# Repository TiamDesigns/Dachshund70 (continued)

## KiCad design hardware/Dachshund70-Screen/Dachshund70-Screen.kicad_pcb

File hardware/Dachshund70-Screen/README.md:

# Dachshund70 screen board

A small board that powers the 2.7" Sharp memory LCD and joins it to the mainboard with one flat cable. KiCad 10
project, 2 layers, 0.8 mm FR4, 21.0 × 34.0 mm with R1 corners.

- **Panel:** Sharp LS027B7DH01 (400 × 240, 2.7", 62.8 × 42.82 × 1.64 mm glass, 58.8 × 35.28 mm picture, about
  173 ppi). It stands on end beside the knob, so the picture is 240 × 400 in portrait. A memory LCD redraws a
  full frame in about 50 ms and holds its picture for a few microwatts, so the firmware treats it like an OLED,
  not like e-paper: no refresh limit, no flashing.
- **Every part is on the bottom side**, facing the mainboard. The top side is a plain ground pour, taped to the
  back of the panel.
- **Same coordinates as the mainboard.** The board is drawn where it sits in the case, straight over the
  mainboard (x 311.0 to 332.0, y 69.2 to 103.2 KiCad mm), so its STEP drops into the case model at the same x
  and y (`python hardware/export_step.py` writes `hardware/step/Dachshund70-Screen.step` with the mainboard's
  origin).

Rev 1.0 of this board (in git history, PR #83) drove the 2.13" GDEY0213B74 e-paper panel instead.

## Circuit

- **5 V supply.** The panel runs from 5 V (VDD and VDDA, 4.8 to 5.5 V). U1, a TI TPS61222 (fixed 5 V boost,
  SC-70-6), makes it from the mainboard's 3V3, with L1 (4.7 µH), C1 (10 µF in) and C2 (10 µF out), as in TI's
  5 V example. FB goes straight to VOUT, as the datasheet says for the fixed versions.
- **Enable.** U1's EN comes from J4 pin 8 (the e-paper overlays' BUSY, P0.24) as VLCD_EN, and R1 (100 kΩ) pulls
  it up to 3V3. The Sharp overlay leaves that pin alone, so the 5 V is always on. The firmware could drive it low
  to cut the panel's power in deep sleep, but then the panel loses its picture.
- **Logic.** The panel takes 3.3 V logic straight (VIH from 2.7 V; Sharp recommends about 3 V). No level shifter.
- **VCOM.** EXTMODE is tied high, so VCOM follows the EXTCOMIN pulse from the MCU (Zephyr's `sharp,ls0xx` driver
  toggles it at 1 Hz).
- **Sharp's capacitors.** C3 (1 µF, VDD), C4 (100 nF, VDDA) and C5 (100 nF, DISP), placed close to J1.
- **Power.** The panel draws about 50 µW holding a picture and about 175 µW updating once a second. With U1's
  5.5 µA quiescent current, the screen costs about 0.03 to 0.08 mA while typing and 20 to 40 µA asleep.

The firmware build is
`-DEXTRA_DTC_OVERLAY_FILE=displays/sharp-ls027b7dh01-portrait.overlay`.

## Cable

The mainboard's J4 is an 8-pin 0.5 mm FFC socket (Hirose FH12-8S-0.5SH(55)), on its top side under the plate's
screen notch. The screen board's J2 is the same socket on its bottom side, at the same x and y (centre
(327.9, 94.9)). Both mouths face −x. The cable leaves J4, loops up through the plate's notch and turns back into
J2: a C-shaped loop.

- Use a **0.5 mm pitch, 8-way FFC with contacts on the same side at both ends** (often called type A). Each
  conductor stays at the same y, so J4 pin n meets J2 pin 9 − n. The schematics already account for that.
- The length still has to be set from the case model: the gap between the two boards plus the loop. Buy a
  few lengths around it; FFCs are cheap.

J4 and the mainboard are unchanged from rev 1.0. Its pins keep their e-paper names in the mainboard schematic; the
Sharp panel uses them like this:

| J4 pin (mainboard) | Mainboard net | MCU pin | J2 pin (screen board) | Screen board net | Panel pin |
| --- | --- | --- | --- | --- | --- |
| 1 | +3V3 | | 8 | +3V3 (U1 input) | |
| 2 | GND | | 7 | GND | 9, 10 |
| 3 | DISP_DIN | P0.21 | 6 | SI | 2 |
| 4 | DISP_CLK | P0.19 | 5 | SCLK | 1 |
| 5 | DISP_CS | P0.20 | 4 | SCS (active high) | 3 |
| 6 | DISP_DC | P0.23 | 3 | EXTCOMIN | 4 |
| 7 | DISP_RST | P0.22 | 2 | DISP | 5 |
| 8 | DISP_BUSY | P0.24 | 1 | VLCD_EN (U1's EN) | |

Panel pins 6 and 7 (VDDA, VDD) and 8 (EXTMODE) are on +5V.

## Geometry

- **The panel's tail.** In landscape the LS027B7DH01's FPC leaves a long edge (the bottom one). Stood on end, that
  edge is on the left. The tail folds back under the glass (Sharp allows bends 0.8 to 6.0 mm from the glass edge,
  inner radius at least 0.45 mm) and runs right into J1.
- **J1** (panel socket, Hirose FH12-10S-0.5SH(55)) is centred at (316.6, 93.7) with its mouth facing −x, toward
  the board's left edge. Its pad row is at x 318.45, from pad 10 at y 91.45 to pad 1 at y 95.95.
- **J1's pins run the other way from the panel's: J1 pin n = panel pin 11 − n.** Looking down on the board,
  the fold puts panel pin 1 at the top (smaller y), where J1's pad 10 is. That assumes pin 1 is on the left of
  the tail when you look at the panel's face in landscape with the tail at the bottom: check it (see below).
- **J2** (cable socket) has its pad row at x 329.75, y 93.15 (pin 8, 3V3) to 96.65 (pin 1, VLCD_EN).
- The board stays left of the radio's antenna (x > 333) and well inside the glass (about x 308 to 351 and y 62
  to 125, if the case thread's 39 mm sidebar holds).

## Routing

The board is hand-routed in `gen_screen.py`.

- The five signals run right from J1, then step down a staircase into J2 under its body. SCLK and SI swap
  order between the two sockets, so SCLK hops over SI on the top layer: the only crossing.
- The boost sits above the sockets: U1 in the middle, L1 to its left, C1 and the 3V3 rail above.
- 3V3 runs from J2 up the right-hand side under J2's body, then along the top of the board.
- On the top layer, apart from the SCLK hop, two tracks cross the ground pour: +5V from the boost down to J1
  and its capacitors, and VLCD_EN from J2 up to U1.
- Track widths are 0.4 mm for SW, 0.3 mm for 3V3, +5V and ground stubs, 0.2 mm for signals. Vias are
  0.6/0.3 mm.

## Mainboard changes

None for the Sharp panel. J4 became an FFC socket in rev 1.0; `move_j4.py` records that one-off edit.

## Status

The board has been checked in KiCad only. Nothing is ordered, made or fitted.

- ERC: 0. DRC with schematic parity and every severity: 0 violations and 0 unconnected items.

## Open checks before ordering

- **Panel FPC: pin 1, contact face and pitch.** From Sharp's drawing, or a panel in hand: which end of the tail
  is pin 1, which face carries the contacts, and the pitch (0.5 mm is assumed). If pin 1 lands at the bottom of
  J1 instead, swap J1's pin map in `gen_screen.py` (`SOCKET`) and reroute. Then check the FH12-10S's contact side
  against the tail's contacts after the fold. Sharp's recommended sockets are SMK CFP-4610-0150F (bottom
  contact) and Molex 51441-1093.
- **Panel tail position and length.** Where along the long edge the tail leaves, and how long it is, so that
  it reaches J1 after the fold. J1 sits at y 93.7, about the middle of the glass's length.
- **FFC against the sockets.** As in rev 1.0: with same-side contacts and the C-shaped loop, J2 and J4 must
  have their contacts on the same side as the cable's contacts at each end.
- **LCSC numbers to confirm or fill:**
  - Filled in: 10 µF C19702, 1 µF C52923, 100 nF C1525, 100 kΩ C25741. Confirm these.
  - Still blank: J1 and J2 (FH12-10S and FH12-8S), U1 (TPS61222DCKR) and L1 (FNR3015S4R7MT).
- **Case.** The screen pocket, window and board pocket in the Fusion model are drawn for the 2.13" e-paper. They
  need the LS027B7DH01's 62.8 × 42.82 mm glass, the folded tail on the left, and this board under it. Then place
  the FFC loop and check the parts' clearance to the plate (it floats ±1 mm).
- **On hardware:** which way up the text comes out (`rotation` in the overlay), and that the picture holds with
  EXTCOMIN at 1 Hz.

## Regenerating

Run with KiCad 10's Python, from the repo root:

```
"C:/Program Files/KiCad/10.0/bin/python.exe" hardware/Dachshund70-Screen/gen_screen.py
```

This rewrites the schematic and the whole board: placement, the routes in `ROUTES` and `VIAS`, and the filled
pours. Then check it:

```
kicad-cli pcb drc --schematic-parity --severity-all Dachshund70-Screen.kicad_pcb
kicad-cli sch erc --severity-all Dachshund70-Screen.kicad_sch
```

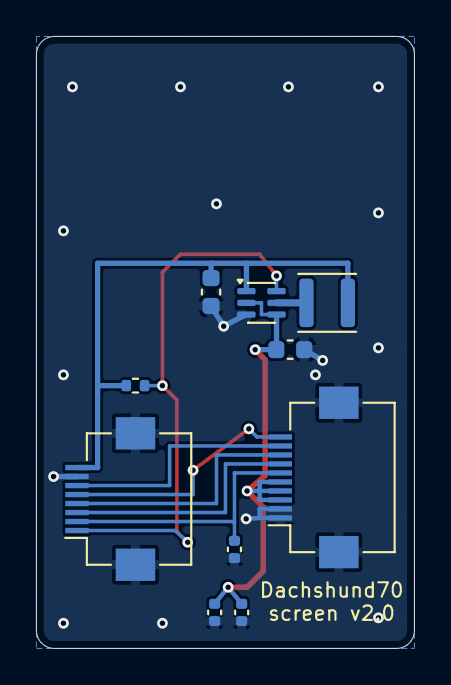
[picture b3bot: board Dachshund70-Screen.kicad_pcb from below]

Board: 2 copper layers, 21.0 x 34.0 mm, 10 parts (10 on the bottom side), 10 nets.

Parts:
C1, C2: 10uF; C_0603_1608Metric
C3: 1uF; C_0402_1005Metric
C4, C5: 100nF; C_0402_1005Metric
J1: Memory LCD (FPC 10P 0.5 mm); Hirose_FH12-10S-0.5SH_1x10-1MP_P0.50mm_Horizontal
J2: Mainboard J4 (FFC 8P 0.5 mm, same side); Hirose_FH12-8S-0.5SH_1x08-1MP_P0.50mm_Horizontal
L1: 4.7uH; L_Changjiang_FNR3015S
R1: 100k; R_0402_1005Metric
U1: TPS61222DCK; SOT-363_SC-70-6

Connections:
+3V3: C1.1, J2.8, L1.1, R1.1, U1.1
+5V: C2.1, C3.1, C4.1, J1.3, J1.4, J1.5, U1.2, U1.4
/DISP: C5.1, J1.6, J2.2
/EXTCOMIN: J1.7, J2.3
/SCLK: J1.10, J2.5
/SCS: J1.8, J2.4
/SI: J1.9, J2.6
/SW: L1.2, U1.5
/VLCD_EN: J2.1, R1.2, U1.6
GND: C1.2, C2.2, C3.2, C4.2, C5.2, J1.1, J1.2, J1.MP, J2.7, J2.MP, U1.3

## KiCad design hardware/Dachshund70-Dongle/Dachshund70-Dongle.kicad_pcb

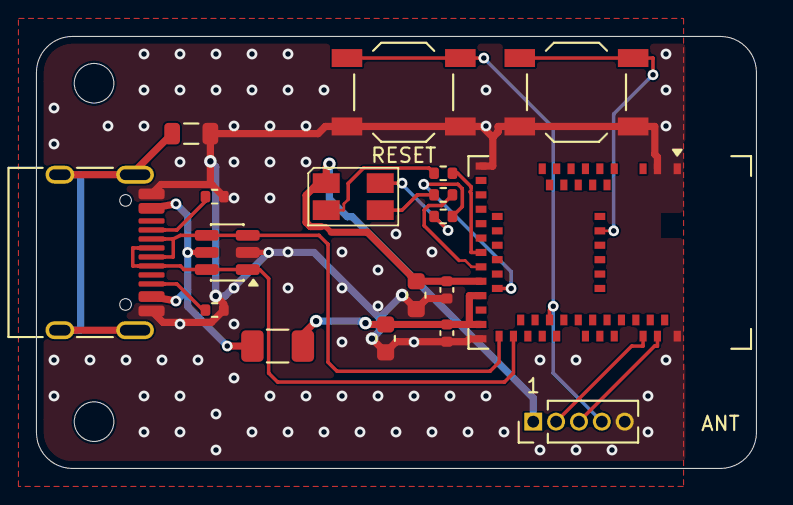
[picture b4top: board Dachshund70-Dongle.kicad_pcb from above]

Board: 2 copper layers, 40.0 x 24.0 mm, 20 parts (0 on the bottom side), 19 nets.

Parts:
C1, C3: 4.7uF; C_0603_1608Metric
C2, C4: 100nF; C_0402_1005Metric
D1: ASMB-MTB0-0A3A2; LED_Avago_PLCC4_3.2x2.8mm_CW
F1: PTC 750mA hold; Fuse_1206_3216Metric
FB1: 600R@100MHz; L_0805_2012Metric
H1, H2: M2; MountingHole_2.2mm_M2
J1: USB-C (HRO TYPE-C-31-M-12); USB_C_Receptacle_HRO_TYPE-C-31-M-12
J2: SWD; PinHeader_1x05_P1.27mm_Vertical
R1, R2: 5.1k; R_0402_1005Metric
R3: 1k; R_0402_1005Metric
R4, R5: 330; R_0402_1005Metric
SW1: Pair; SW_SPST_TL3342
SW2: Reset; SW_SPST_TL3342
U1: USBLC6-2SC6; SOT-23-6
U2: MDBT50Q-P1MV2; Raytac_MDBT50Q

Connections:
/+3V3: C3.1, C4.1, D1.1, J2.1, U2.28
/CC1: J1.A5, R1.1
/CC2: J1.B5, R2.1
/D+: J1.A6, J1.B6, U1.1, U1.6, U2.35
/D-: J1.A7, J1.B7, U1.3, U1.4, U2.34
/LED_B: R5.2, U2.29
/LED_BK: D1.2, R5.1
/LED_G: R4.2, U2.26
/LED_GK: D1.3, R4.1
/LED_R: R3.2, U2.24
/LED_RK: D1.4, R3.1
/NRESET: J2.4, SW2.1, U2.40
/PAIR: SW1.1, U2.57
/SHIELD: FB1.1, J1.SH
/SWDCLK: J2.3, U2.53
/SWDIO: J2.2, U2.51
/VBUS: C1.1, C2.1, F1.2, U2.30, U2.32
/VBUS_RAW: F1.1, J1.A4, J1.A9, J1.B4, J1.B9, U1.5
GND: C1.2, C2.2, C3.2, C4.2, FB1.2, J1.A1, J1.A12, J1.B1, J1.B12, J2.5, R1.2, R2.2, SW1.2, SW2.2, U1.2, U2.1, U2.2, U2.15, U2.33, U2.55

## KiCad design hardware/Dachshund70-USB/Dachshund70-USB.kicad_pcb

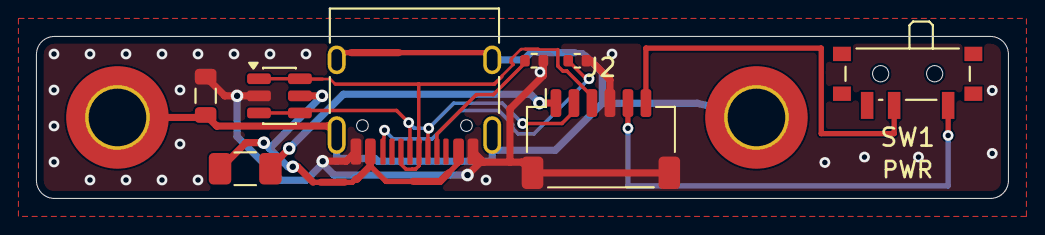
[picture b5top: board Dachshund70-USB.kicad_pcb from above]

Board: 2 copper layers, 54.0 x 9.0 mm, 10 parts (0 on the bottom side), 10 nets.

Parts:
F1: PTC 750mA hold; Fuse_1206_3216Metric
FB1: 600R@100MHz; L_0805_2012Metric
H1, H2: M3; MountingHole_3.2mm_M3_ISO7380_Pad_TopBottom
J1: USB-C (HRO TYPE-C-31-M-12); USB_C_Receptacle_HRO_TYPE-C-31-M-12
J2: Mainboard (JST-SH 6P); JST_SH_SM06B-SRSS-TB_1x06-1MP_P1.00mm_Horizontal
R1, R2: 5.1k; R_0402_1005Metric
SW1: Power; SW_SPDT_PCM12
U1: USBLC6-2SC6; SOT-23-6

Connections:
/CC1: J1.A5, R1.1
/CC2: J1.B5, R2.1
/D+: J1.A6, J1.B6, J2.3, U1.1, U1.6
/D-: J1.A7, J1.B7, J2.2, U1.3, U1.4
/SHIELD: FB1.1, H1.1, H2.1, J1.SH
/VBAT: J2.5, SW1.1
/VBAT_SW: J2.6, SW1.2
/VBUS: F1.2, J2.1
/VBUS_RAW: F1.1, J1.A4, J1.A9, J1.B4, J1.B9, U1.5
GND: FB1.2, J1.A1, J1.A12, J1.B1, J1.B12, J2.4, J2.MP, R1.2, R2.2, U1.2

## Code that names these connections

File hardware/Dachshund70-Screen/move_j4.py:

"""One-off edit of the mainboard: J4, the hand-wired 2.54 mm display header, becomes an
8-pin 0.5 mm FFC socket for the screen board (Hirose FH12-8S, top side, under the plate notch) and the
eight display nets are rerouted to it. Kept for the record; run it once, in KiCad 10's Python, from the
repo root. The schematic side is done separately (J4's symbol becomes Conn_01x08_MountingPin, MP to GND).

J4's pins sit at the same x and y as the screen board's J2 (the FFC loops round between them), so pin n
here meets J2 pin 9 - n. Pin 1 (3V3) is at the back (smaller y), pin 8 (BUSY) at the front. The
socket sits under the plate's screen notch, 2.7 mm behind the SWD header J3 so its body clears J3.
"""
import pcbnew

PCB = "hardware/Dachshund70/Dachshund70.kicad_pcb"
FP_DIR = "/usr/share/kicad/footprints/Connector_FFC-FPC.pretty"
FP_NAME = "Hirose_FH12-8S-0.5SH_1x08-1MP_P0.50mm_Horizontal"
XY = (327.9, 94.9)           # pads y 93.15-96.65, clear of J3 (the SWD header, from y 100.4)
M, F = pcbnew.ToMM, pcbnew.FromMM

b = pcbnew.LoadBoard(PCB)
nets = {n: b.FindNet(n) for n in ("+3V3", "GND", "/DISP_DIN", "/DISP_CLK", "/DISP_CS", "/DISP_DC", "/DISP_RST",
                                  "/DISP_BUSY")}
DISP = [n for n in nets if n.startswith("/DISP")]


TRACKS = list(b.GetTracks())    # looked up once: pcbnew's track list can't be re-read after a Remove
REMOVE = []


def P(x, y):
    return pcbnew.VECTOR2I(F(x), F(y))


def near(a, xy, tol=0.002):
    return abs(M(a.x) - xy[0]) < tol and abs(M(a.y) - xy[1]) < tol


def find_track(net, layer, a, c):
    for t in TRACKS:
        if t in REMOVE:
            continue
        if t.GetClass() == "PCB_VIA" or t.GetNetname() != net or t.GetLayerName() != layer:
            continue
        if (near(t.GetStart(), a) and near(t.GetEnd(), c)) or (near(t.GetStart(), c) and near(t.GetEnd(), a)):
            return t
    raise SystemExit("no track %s %s %r %r" % (net, layer, a, c))


def find_via(net, xy):
    for t in TRACKS:
        if t.GetClass() == "PCB_VIA" and t.GetNetname() == net and near(t.GetPosition(), xy, 0.01):
            return t
    raise SystemExit("no via %s %r" % (net, xy))


def drop_track(net, layer, a, c):
    REMOVE.append(find_track(net, layer, a, c))


def move_end(net, layer, a, c, old, new):
    """Move the end of track a-c that sits at old to new."""
    t = find_track(net, layer, a, c)
    if near(t.GetStart(), old):
        t.SetStart(P(*new))
    else:
        t.SetEnd(P(*new))


def track(net, layer, pts, w):
    for (ax, ay), (cx, cy) in zip(pts, pts[1:]):
        t = pcbnew.PCB_TRACK(b)
        t.SetStart(P(ax, ay))
        t.SetEnd(P(cx, cy))
        t.SetWidth(F(w))
        t.SetLayer(pcbnew.F_Cu if layer == "F" else pcbnew.B_Cu)
        t.SetNet(nets[net])
        b.Add(t)


def via(net, x, y):
    v = pcbnew.PCB_VIA(b)
    v.SetPosition(P(x, y))
    v.SetWidth(F(0.6))
    v.SetDrill(F(0.3))
    v.SetNet(nets[net])
    b.Add(v)


# ---- the old header and every F.Cu stub to it
old = b.FindFootprintByReference("J4")
path = old.GetPath()
for t in TRACKS:
    if t.GetClass() != "PCB_VIA" and t.GetLayerName() == "F.Cu" and t.GetNetname() in DISP:
        if M(t.GetStart().y) > 104.0 or M(t.GetEnd().y) > 104.0:      # the display runs below y 104 only
            REMOVE.append(t)
for n, xy in (("/DISP_DIN", (304.126, 111.2844)), ("/DISP_CLK", (303.4476, 109.2921)),
              ("/DISP_CS", (302.8174, 107.3224)), ("/DISP_BUSY", (302.2158, 105.4471))):
    REMOVE.append(find_via(n, xy))
for gx, gy in ((323.85, 95.25), (321.150933, 109.600499), (302.0277, 108.961626)):   # GND stitching in the way
    REMOVE.append(find_via("GND", (gx, gy)))
b.Remove(old)

# 3V3 used to pass through the header's pin 1 on its way to J3 (F.Cu in, B.Cu out): a via there now

# B.Cu ends of the four F.Cu runs: the vias move so the runs come out DIN on top, BUSY at the bottom
drop_track("/DISP_DIN", "B.Cu", (304.126, 111.2844), (304.3172, 111.0932))
move_end("/DISP_DIN", "B.Cu", (304.3172, 111.0932), (304.3172, 80.2828), (304.3172, 111.0932), (304.3172, 105.81))
track("/DISP_DIN", "B", [(304.3172, 105.81), (304.126, 106.0)], 0.25)          # clear of ROW4 at x 304.77
move_end("/DISP_CLK", "B.Cu", (303.4476, 109.2921), (303.4476, 88.3391), (303.4476, 109.2921), (303.4476, 106.5))
track("/DISP_CLK", "B", [(303.4476, 106.5), (303.5476, 106.8)], 0.25)
drop_track("/DISP_CS", "B.Cu", (302.8636, 107.2762), (302.8174, 107.3224))
move_end("/DISP_CS", "B.Cu", (302.8636, 88.3939), (302.8636, 107.2762), (302.8636, 107.2762), (302.8636, 107.58))
move_end("/DISP_BUSY", "B.Cu", (302.2158, 105.4471), (302.2158, 88.3849), (302.2158, 105.4471), (302.2158, 109.4))
# DC: its B.Cu run from the north now stops at a via at y 108.2
drop_track("/DISP_DC", "B.Cu", (321.81, 112.5), (323.8355, 110.4745))
move_end("/DISP_DC", "B.Cu", (323.8355, 110.4745), (323.8355, 100.5464), (323.8355, 110.4745), (323.8355, 108.2))
# RST: its B.Cu run now stops at a via at y 108.8 instead of looping south of the old header
for a, c in (((324.35, 112.5), (322.0256, 114.8244)), ((322.0256, 114.8244), (309.2719, 114.8244)),
             ((309.2719, 114.8244), (307.9155, 113.468)), ((307.9155, 113.468), (307.9155, 113.1497)),
             ((307.9155, 113.1497), (307.9155, 112.8313)), ((307.9155, 112.8313), (307.9155, 109.0255)),
             ((307.9155, 109.0255), (309.5086, 107.4324))):
    drop_track("/DISP_RST", "B.Cu", a, c)
track("/DISP_RST", "B", [(309.5086, 107.4324), (309.5086, 108.8)], 0.25)
for n, x, y in (("+3V3", 309.11, 112.5), ("/DISP_DIN", 304.126, 106.0), ("/DISP_CLK", 303.5476, 106.8), ("/DISP_CS", 302.8636, 107.58),
                ("/DISP_BUSY", 302.2158, 109.4), ("/DISP_DC", 323.8355, 108.2), ("/DISP_RST", 309.5086, 108.8)):
    via(n, x, y)

for t in REMOVE:
    b.Remove(t)

# ---- the new socket
fp = pcbnew.FootprintLoad(FP_DIR, FP_NAME)
fp.SetFPIDAsString("Connector_FFC-FPC:" + FP_NAME)
fp.SetReference("J4")
fp.SetValue("Screen board")
fp.GetField(pcbnew.FIELD_T_DATASHEET).SetText(
    "https://www.hirose.com/product/document?clcode=CL0580-1255-6-55&productname=FH12-8S-0.5SH(55)&series=FH12"
    "&documenttype=Catalog&lang=en&documentid=D31690_en")
fp.GetField(pcbnew.FIELD_T_DESCRIPTION).SetText(
    "Screen board cable port: 8-pin 0.5 mm FFC, same-side contacts "
    "(pin 1 3V3, 2 GND, 3 DIN, 4 CLK, 5 CS, 6 DC, 7 RST, 8 BUSY)")
for fname, fval in (("MPN", "Hirose FH12-8S-0.5SH(55)"), ("LCSC", "")):
    fld = pcbnew.PCB_FIELD(fp, fp.GetNextFieldOrdinal(), fname)
    fld.SetText(fval)
    fld.SetVisible(False)
    fld.SetLayer(pcbnew.F_Fab)
    fp.Add(fld)
fp.SetPath(path)
fp.SetPosition(P(*XY))
b.Add(fp)
for r in (90, 270):          # pads on the +x side, so the mouth faces -x
    fp.SetOrientationDegrees(r)
    p1 = [p for p in fp.Pads() if p.GetNumber() == "1"][0]
    if M(p1.GetPosition().x) > XY[0]:
        break
PIN = {"1": "+3V3", "2": "GND", "3": "/DISP_DIN", "4": "/DISP_CLK", "5": "/DISP_CS", "6": "/DISP_DC",
       "7": "/DISP_RST", "8": "/DISP_BUSY", "MP": "GND"}
for p in fp.Pads():
    p.SetNet(nets[PIN[p.GetNumber()]])
    if p.GetNumber() != "MP":
        print("pad", p.GetNumber(), M(p.GetPosition().x), M(p.GetPosition().y))
fp.Reference().SetPosition(P(XY[0] - 1.6, XY[1]))
fp.Reference().SetTextAngleDegrees(90)

# ---- routes. Rows under the socket body; 3V3, DIN, CLK and CS go down between J3 and the front mounting
# pad, DC, RST and BUSY right of it, then jog left under the pad; all run west under J3.
PX = 329.75                  # pad centres
W = 0.18
track("+3V3", "F", [(323.0, 106.0), (323.85, 106.0), (323.85, 93.15), (PX, 93.15)], 0.25)
track("/DISP_DIN", "F", [(PX, 94.15), (324.29, 94.15), (324.29, 106.8), (304.926, 106.8), (304.126, 106.0)], W)
track("/DISP_CLK", "F", [(PX, 94.65), (324.68, 94.65), (324.68, 107.19), (303.9376, 107.19), (303.5476, 106.8)], W)
track("/DISP_CS", "F", [(PX, 95.15), (325.07, 95.15), (325.07, 107.58), (302.8636, 107.58)], W)
track("/DISP_DC", "F", [(PX, 95.65), (327.95, 95.65), (327.95, 99.85), (325.6, 102.2), (325.6, 108.2),
                        (323.8355, 108.2)], W)
track("/DISP_RST", "F", [(PX, 96.15), (328.55, 96.15), (328.55, 99.85), (326.2, 102.2), (326.2, 108.8),
                         (309.5086, 108.8)], W)
# GND: the front mounting pad sits in a pocket of the pour, and pin 2 between two tracks; a via each
track("GND", "F", [(326.5, 98.55), (325.8, 97.3)], 0.3)
track("GND", "F", [(PX, 93.65), (331.0, 93.65)], 0.2)
via("GND", 325.8, 97.3)
via("GND", 331.0, 93.65)
track("/DISP_BUSY", "F", [(PX, 96.65), (PX, 97.1), (329.15, 97.7), (329.15, 99.85), (326.8, 102.2), (326.8, 109.4),
                          (302.2158, 109.4)], W)

b.BuildConnectivity()
pcbnew.ZONE_FILLER(b).Fill(b.Zones())
b.Save(PCB)
print("saved")
